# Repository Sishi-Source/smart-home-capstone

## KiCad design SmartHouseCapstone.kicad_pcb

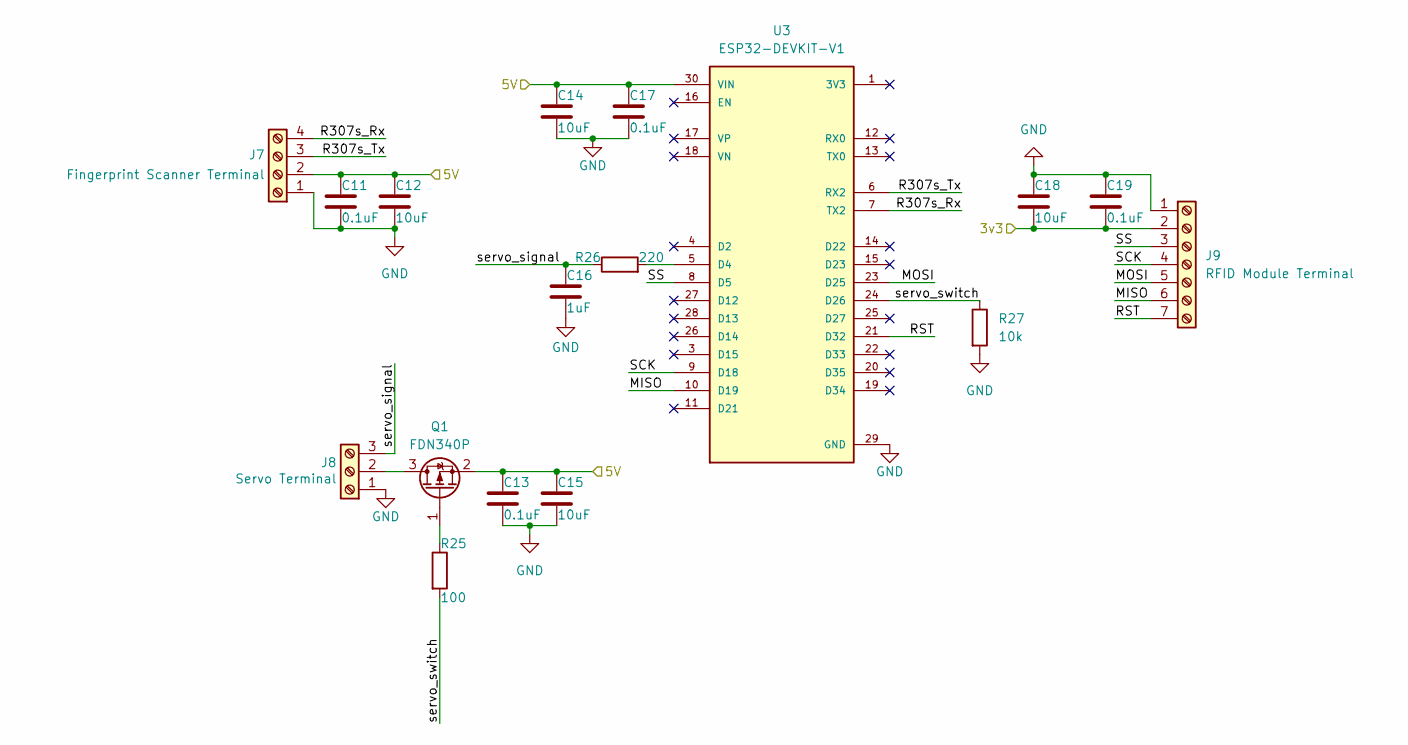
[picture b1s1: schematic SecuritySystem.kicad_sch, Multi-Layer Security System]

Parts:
C11, C13, C17, C19: 0.1uF; C_0603_1608Metric_Pad1.08x0.95mm_HandSolder
C12, C14, C15, C18: 10uF; C_0805_2012Metric_Pad1.18x1.45mm_HandSolder
C16: 1uF; C_0805_2012Metric_Pad1.18x1.45mm_HandSolder
J7: Fingerprint Scanner Terminal; TerminalBlock_Phoenix_MKDS-1,5-4_1x04_P5.00mm_Horizontal
J8: Servo Terminal; TerminalBlock_Phoenix_MKDS-1,5-3_1x03_P5.00mm_Horizontal
J9: RFID Module Terminal; TerminalBlock_Phoenix_MKDS-1,5-7_1x07_P5.00mm_Horizontal
Q1: FDN340P; SOT-23_Handsoldering
R25: 100; R_Axial_DIN0207_L6.3mm_D2.5mm_P7.62mm_Horizontal
R26: 220; R_Axial_DIN0207_L6.3mm_D2.5mm_P7.62mm_Horizontal
R27: 10k; R_Axial_DIN0207_L6.3mm_D2.5mm_P7.62mm_Horizontal
U3: ESP32-DEVKIT-V1; MODULE_ESP32_DEVKIT_V1; PARTREV N/A

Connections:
/Automatic Garage Door/5V: C11.1, C12.1, C13.1, C14.1, C15.1, C17.1, J7.2, Q1.2 (S), U3.30 (VIN); also elsewhere on the board
/Lighting Control System/3v3: C18.2, C19.2, J9.2; also elsewhere on the board
/Security System/MISO: J9.6, U3.10 (D19)
/Security System/MOSI: J9.5, U3.23 (D25)
/Security System/R307s_Rx: J7.4, U3.7 (TX2)
/Security System/R307s_Tx: J7.3, U3.6 (RX2)
/Security System/RST: J9.7, U3.21 (D32)
/Security System/SCK: J9.4, U3.9 (D18)
/Security System/SS: J9.3, U3.8 (D5)
/Security System/servo_signal: C16.1, J8.3, R26.1
/Security System/servo_switch: R25.2, R27.1, U3.24 (D26)
GND: C11.2, C12.2, C13.2, C14.2, C15.2, C16.2, C17.2, C18.1, C19.1, J7.1, J8.1, J9.1, R27.2, U3.29 (GND); also elsewhere on the board
unnamed: J8.2, Q1.3 (D)
unnamed: Q1.1 (G), R25.1
unnamed: R26.2, U3.5 (D4)

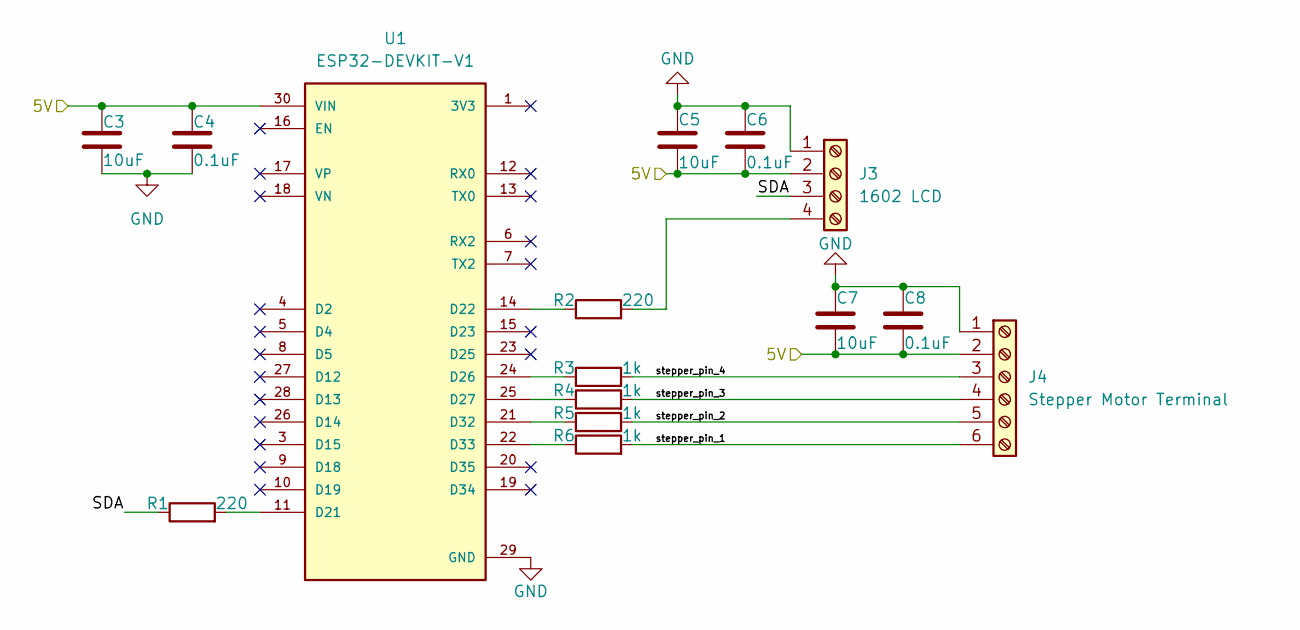
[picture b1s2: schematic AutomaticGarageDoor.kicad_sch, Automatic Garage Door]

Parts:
C3, C5, C7: 10uF; C_0805_2012Metric_Pad1.18x1.45mm_HandSolder
C4, C6, C8: 0.1uF; C_0603_1608Metric_Pad1.08x0.95mm_HandSolder
J3: 1602 LCD; TerminalBlock_Phoenix_MKDS-1,5-4_1x04_P5.00mm_Horizontal
J4: Stepper Motor Terminal; TerminalBlock_Phoenix_MKDS-1,5-6_1x06_P5.00mm_Horizontal
R1, R2: 220; R_Axial_DIN0207_L6.3mm_D2.5mm_P7.62mm_Horizontal
R3, R4, R5, R6: 1k; R_Axial_DIN0207_L6.3mm_D2.5mm_P7.62mm_Horizontal
U1: ESP32-DEVKIT-V1; MODULE_ESP32_DEVKIT_V1; PARTREV N/A

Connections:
/Automatic Garage Door/5V: C3.1, C4.1, C5.2, C6.2, C7.2, C8.2, J3.2, J4.2, U1.30 (VIN); also elsewhere on the board
/Automatic Garage Door/SDA: J3.3, R1.1
/Automatic Garage Door/stepper_pin_1: J4.6, R6.2
/Automatic Garage Door/stepper_pin_2: J4.5, R5.2
/Automatic Garage Door/stepper_pin_3: J4.4, R4.2
/Automatic Garage Door/stepper_pin_4: J4.3, R3.2
GND: C3.2, C4.2, C5.1, C6.1, C7.1, C8.1, J3.1, J4.1, U1.29 (GND); also elsewhere on the board
unnamed: J3.4, R2.2
unnamed: R1.2, U1.11 (D21)
unnamed: R2.1, U1.14 (D22)
unnamed: R3.1, U1.24 (D26)
unnamed: R4.1, U1.25 (D27)
unnamed: R5.1, U1.21 (D32)
unnamed: R6.1, U1.22 (D33)

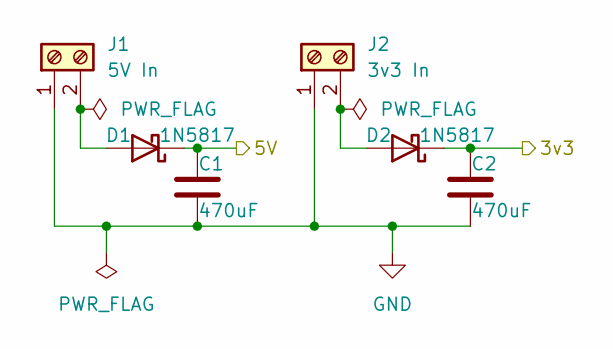
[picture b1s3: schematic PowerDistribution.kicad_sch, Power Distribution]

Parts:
C1, C2: 470uF; C_Radial_D8.0mm_H11.5mm_P3.50mm
D1, D2: 1N5817; D_DO-41_SOD81_P10.16mm_Horizontal
J1: 5V In; TerminalBlock_Phoenix_MKDS-1,5-2_1x02_P5.00mm_Horizontal
J2: 3v3 In; TerminalBlock_Phoenix_MKDS-1,5-2_1x02_P5.00mm_Horizontal

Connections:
/Automatic Garage Door/5V: C1.1, D1.1 (K); also elsewhere on the board
/Lighting Control System/3v3: C2.1, D2.1 (K); also elsewhere on the board
GND: C1.2, C2.2, J1.1, J2.1; also elsewhere on the board
unnamed: D1.2 (A), J1.2
unnamed: D2.2 (A), J2.2

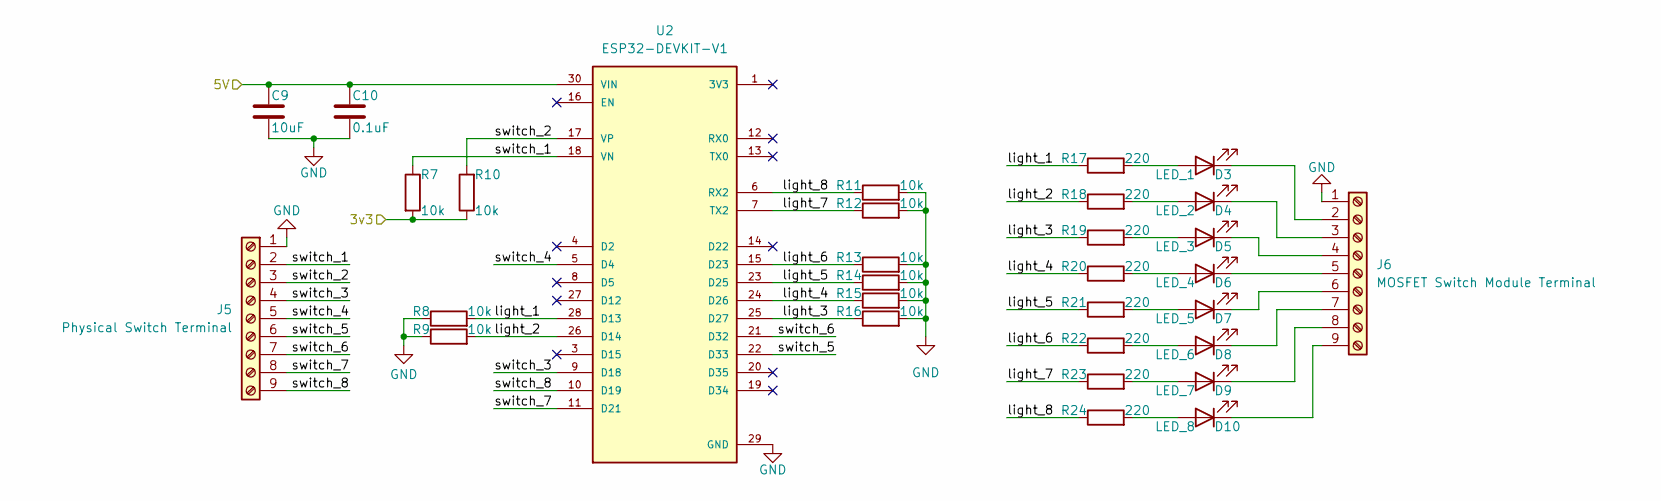
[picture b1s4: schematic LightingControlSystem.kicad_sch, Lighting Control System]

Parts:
C9: 10uF; C_0805_2012Metric_Pad1.18x1.45mm_HandSolder
C10: 0.1uF; C_0603_1608Metric_Pad1.08x0.95mm_HandSolder
D3: LED_1; LED_D3.0mm_Clear
D4: LED_2; LED_D3.0mm_Clear
D5: LED_3; LED_D3.0mm_Clear
D6: LED_4; LED_D3.0mm_Clear
D7: LED_5; LED_D3.0mm_Clear
D8: LED_6; LED_D3.0mm_Clear
D9: LED_7; LED_D3.0mm_Clear
D10: LED_8; LED_D3.0mm_Clear
J5: Physical Switch Terminal; TerminalBlock_Phoenix_MKDS-1,5-9_1x09_P5.00mm_Horizontal
J6: MOSFET Switch Module Terminal; TerminalBlock_Phoenix_MKDS-1,5-9_1x09_P5.00mm_Horizontal
R7, R8, R9, R10, R11, R12, R13, R14, R15, R16: 10k; R_Axial_DIN0207_L6.3mm_D2.5mm_P7.62mm_Horizontal
R17, R18, R19, R20, R21, R22, R23, R24: 220; R_Axial_DIN0207_L6.3mm_D2.5mm_P7.62mm_Horizontal
U2: ESP32-DEVKIT-V1; MODULE_ESP32_DEVKIT_V1; PARTREV N/A

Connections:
/Automatic Garage Door/5V: C9.1, C10.1, U2.30 (VIN); also elsewhere on the board
/Lighting Control System/3v3: R7.2, R10.1; also elsewhere on the board
/Lighting Control System/light_1: R8.2, R17.1, U2.28 (D13)
/Lighting Control System/light_2: R9.2, R18.1, U2.26 (D14)
/Lighting Control System/light_3: R16.1, R19.1, U2.25 (D27)
/Lighting Control System/light_4: R15.1, R20.1, U2.24 (D26)
/Lighting Control System/light_5: R14.1, R21.1, U2.23 (D25)
/Lighting Control System/light_6: R13.1, R22.1, U2.15 (D23)
/Lighting Control System/light_7: R12.1, R23.1, U2.7 (TX2)
/Lighting Control System/light_8: R11.1, R24.1, U2.6 (RX2)
/Lighting Control System/switch_1: J5.2, R7.1, U2.18 (VN)
/Lighting Control System/switch_2: J5.3, R10.2, U2.17 (VP)
/Lighting Control System/switch_3: J5.4, U2.9 (D18)
/Lighting Control System/switch_4: J5.5, U2.5 (D4)
/Lighting Control System/switch_5: J5.6, U2.22 (D33)
/Lighting Control System/switch_6: J5.7, U2.21 (D32)
/Lighting Control System/switch_7: J5.8, U2.11 (D21)
/Lighting Control System/switch_8: J5.9, U2.10 (D19)
GND: C9.2, C10.2, J5.1, J6.1, R8.1, R9.1, R11.2, R12.2, R13.2, R14.2, R15.2, R16.2, U2.29 (GND); also elsewhere on the board
unnamed: D3.2 (A), R17.2
unnamed: D3.1 (K), J6.2
unnamed: D4.2 (A), R18.2
unnamed: D4.1 (K), J6.3
unnamed: D5.2 (A), R19.2
unnamed: D5.1 (K), J6.4
unnamed: D6.2 (A), R20.2
unnamed: D6.1 (K), J6.5
unnamed: D7.2 (A), R21.2
unnamed: D7.1 (K), J6.6
unnamed: D8.2 (A), R22.2
unnamed: D8.1 (K), J6.7
unnamed: D9.2 (A), R23.2
unnamed: D9.1 (K), J6.8
unnamed: D10.2 (A), R24.2
unnamed: D10.1 (K), J6.9

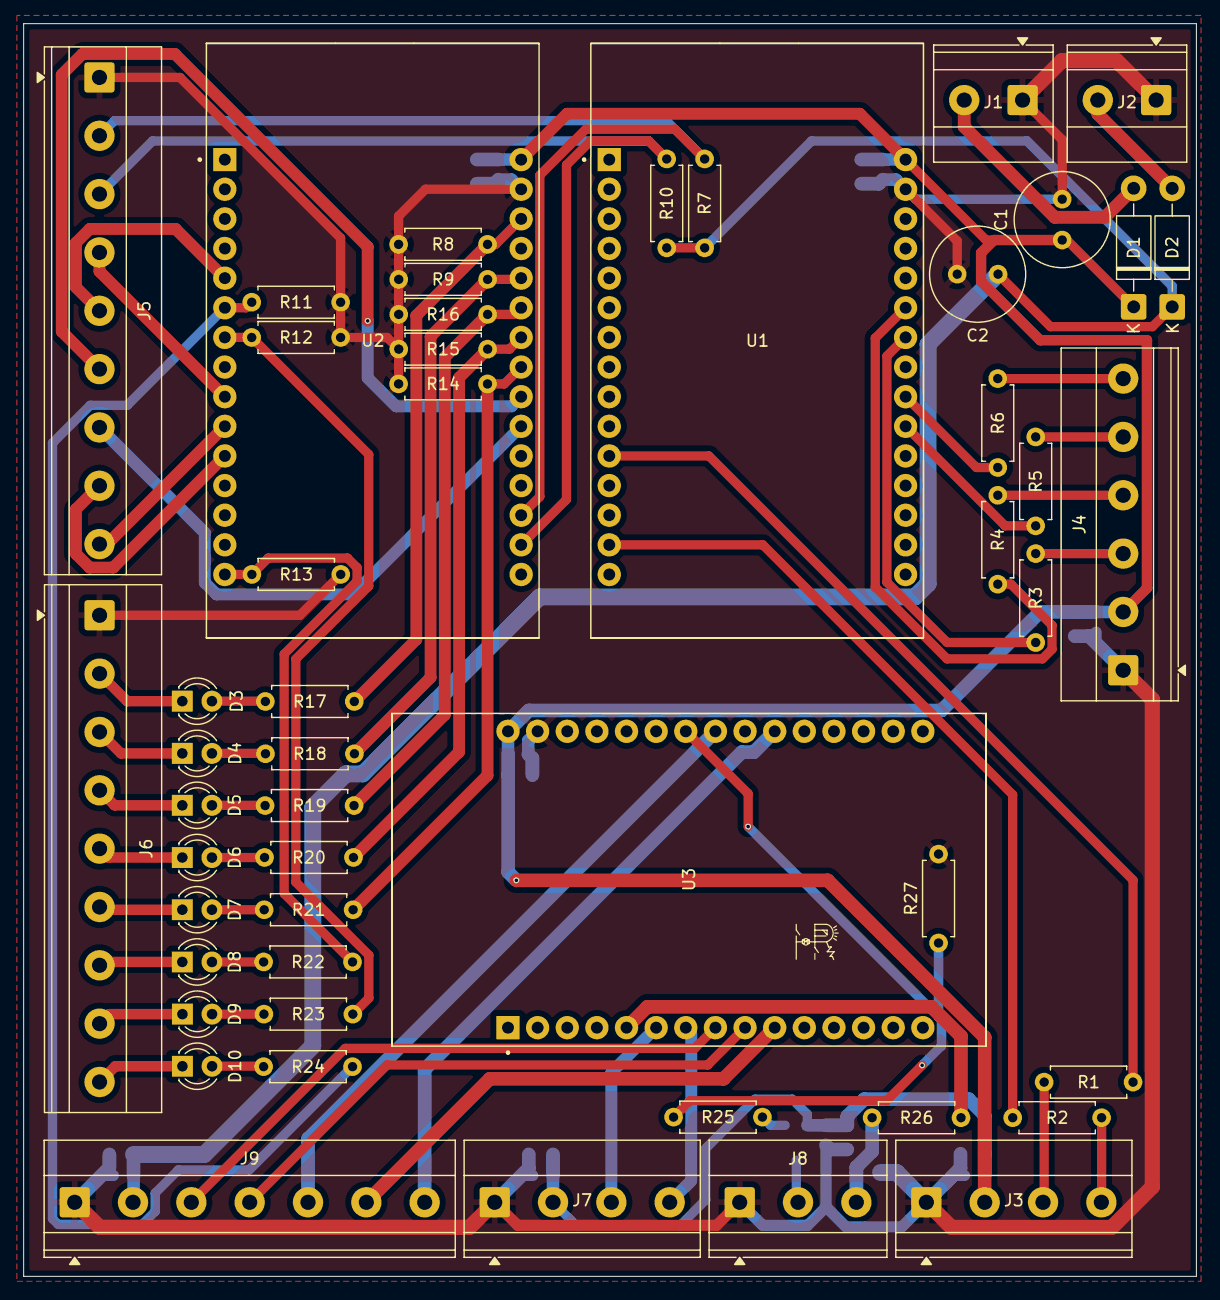
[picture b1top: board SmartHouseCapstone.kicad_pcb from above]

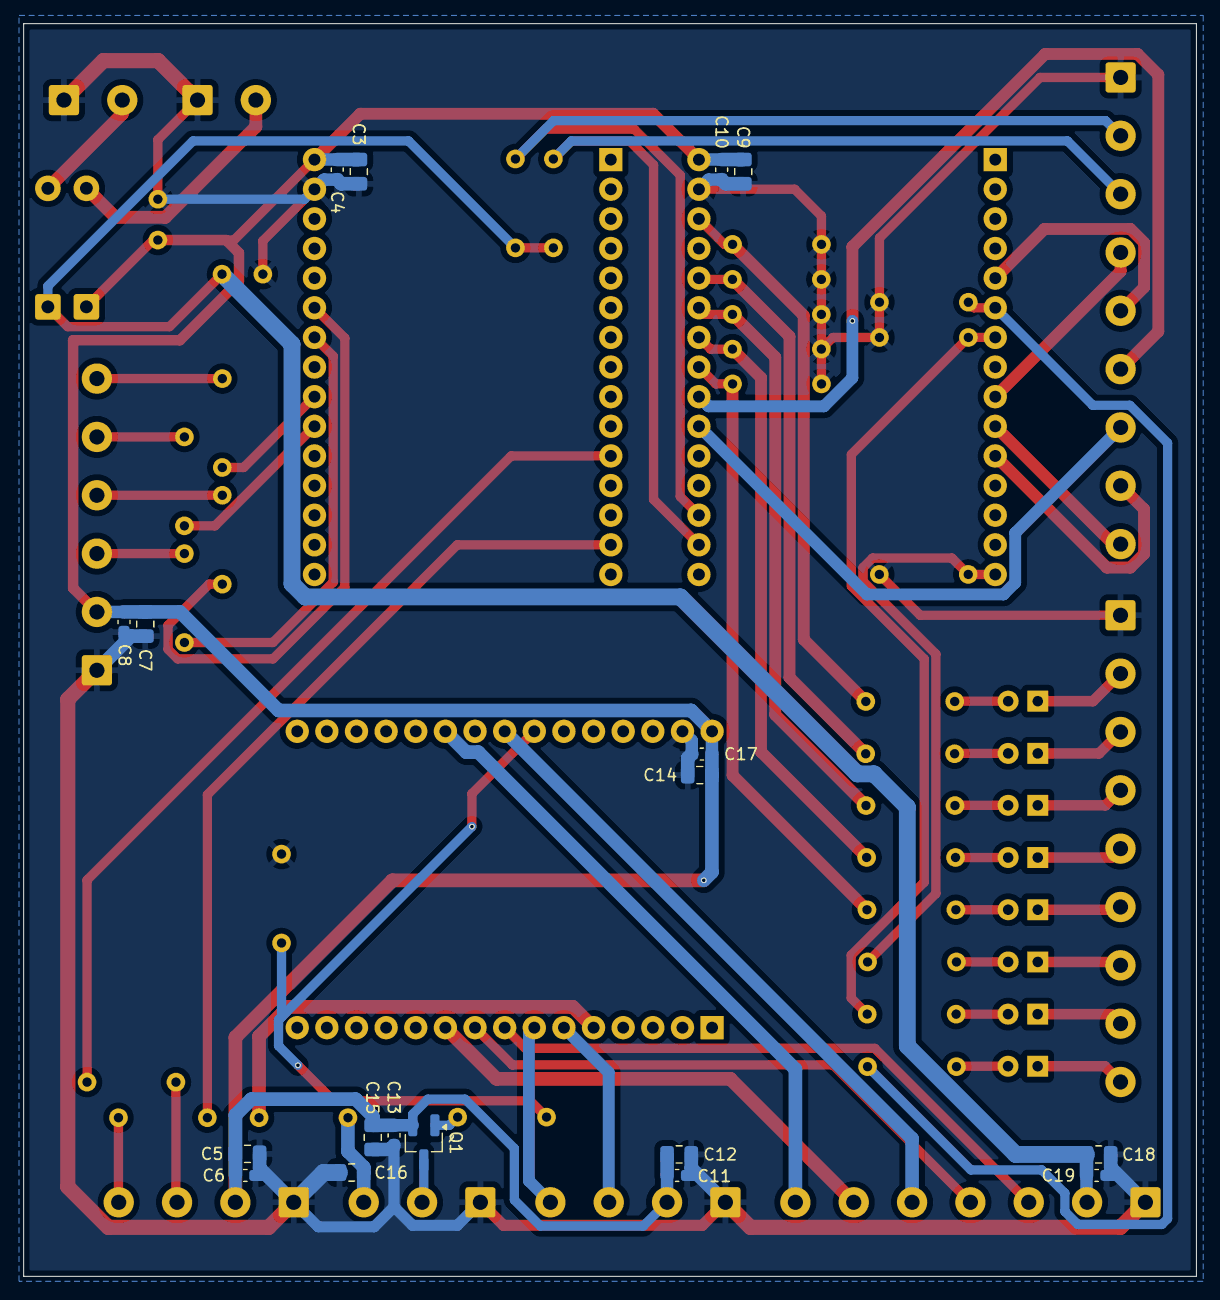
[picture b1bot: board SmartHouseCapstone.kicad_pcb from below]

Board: 2 copper layers, 100.5 x 107.4 mm, 69 parts (18 on the bottom side), 61 nets.

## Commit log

2025-11-03 first revision of Smart Home Control Board
2025-11-03 first revision of Smart House Control Board
2025-11-03 fixed git init mistake [first was a different directory]
2025-11-03 schematic lock deleted??
2025-11-03 revision 1
    added pull-down resistor to FDN430P MosFET Gate
    revised pcb layout
    revised schematic layout
    generated new BOM
    generated new Backup
2025-11-03 updated gerber files
    re-add of resistor footprints -- for some reason it was removed
    re-add of the new pull-down resistor R27 -- for some reason it was not
    in the schematic but it exists in pcb
2025-11-04 revision 2
    modified pull-up/pull-down resistor values
    modified switch1/switch2 input voltage from 5V to 3v3
    added proper sheet detail (designer, cc license)
2025-11-04 updated pcb layout page setup
    added cc license
    added proper title/revision
    added designer name
2025-11-05 pcb revision 3
    added designer and logo in pcb silkscreen

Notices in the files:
AutomaticGarageDoor.kicad_sch:
Released under the Creative Commons
https://creativecommons.org/licenses/by-sa/4.0
